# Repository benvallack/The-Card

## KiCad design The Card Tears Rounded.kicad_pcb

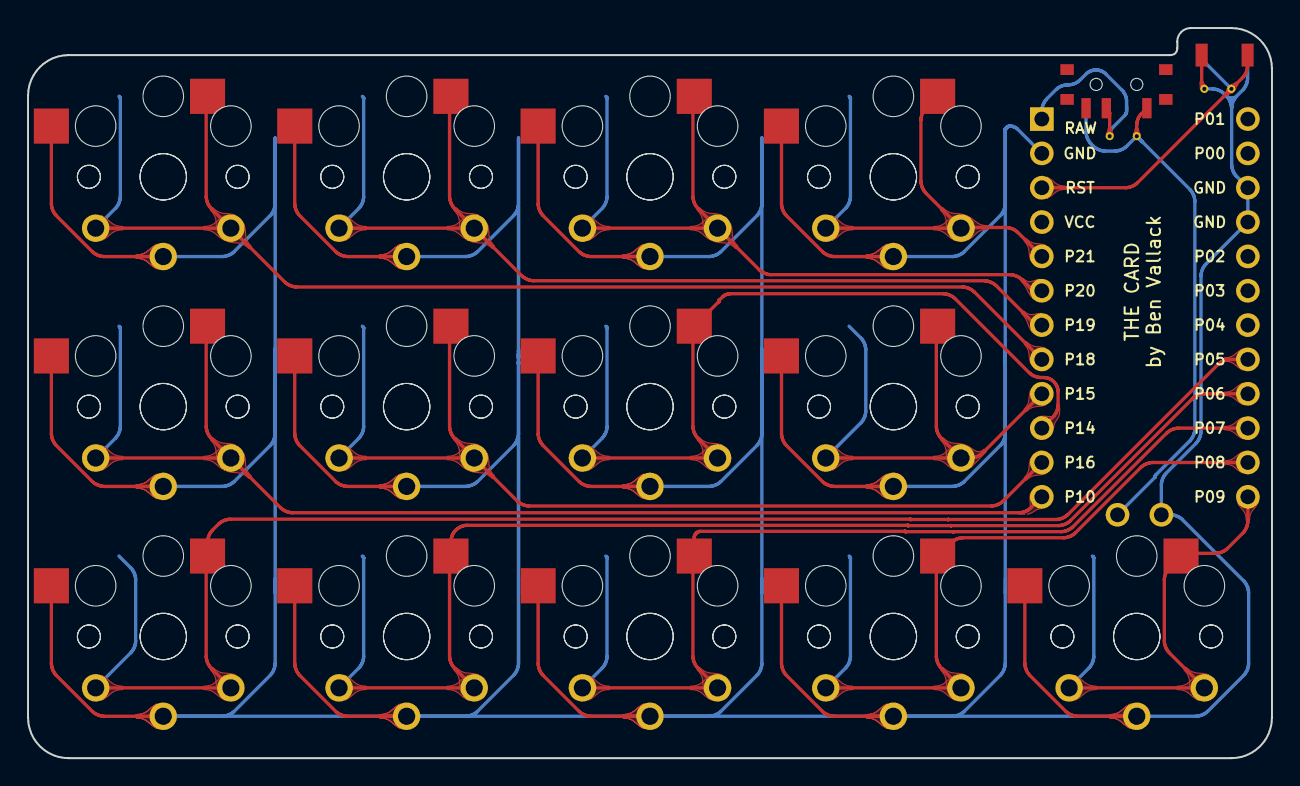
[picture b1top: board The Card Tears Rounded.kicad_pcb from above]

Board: 2 copper layers, 92.0 x 54.0 mm, 27 parts (0 on the bottom side), 14 nets.

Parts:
MCU1: ProMicro
S1, S2, S3, S4, S5, S6, S7, S8, S9, S10, S11, S12, S13, S14, S15, S16, S17, S18, S19, S20, S21, S22, S23, S24, S25, S26: PG1350

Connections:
GND: MCU1.2, MCU1.15, MCU1.16, S1.2, S2.2, S3.2, S4.2, S5.2, S6.2, S7.2, S8.2, S9.2, S10.2, S11.2, S12.2, S13.2, S14.2, S15.2, S16.2, S17.2, S18.2, S19.2, S20.2, S21.2, S22.2, S23.2, S24.2, S25.2, S26.2
P5: MCU1.20, S1.1, S2.1
P6: MCU1.21, S7.1, S8.1
P7: MCU1.22, S13.1, S14.1
P8: MCU1.23, S19.1, S20.1
P9: MCU1.24, S25.1, S26.1
P10: MCU1.12, S3.1, S4.1
P14: MCU1.10, S15.1, S16.1
P15: MCU1.9, S21.1, S22.1
P16: MCU1.11, S9.1, S10.1
P18: MCU1.8, S5.1, S6.1
P19: MCU1.7, S11.1, S12.1
P20: MCU1.6, S17.1, S18.1
P21: MCU1.5, S23.1, S24.1
